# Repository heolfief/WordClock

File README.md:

# 8x8 Dot Matrix Word Clock
This is an AVR based mini word clock featuring:
* Real Time Clock (DS3231)
* LiPo battery with integrated USB charging circuit
* low battery sensing

The unit is composed of two stacked PCB and one 8x8 dot-matrix display module.

The Hardware folder is composed of Autodesk Eagle CAD files (schematics and PCB) and of Bill Of Materials.

The Software folder is composed of Atmel Studio 7.0 project files, including libraries and hex file.

The I2C-master-lib is from user g4lvanix on Github ([github.com/g4lvanix/I2C-master-lib](http://github.com/g4lvanix/I2C-master-lib)). However, he does not include any licence in his repository therefore all rights for this library belongs to him.
All other libraries included are under the licence descibed in the LICENCE.md file.

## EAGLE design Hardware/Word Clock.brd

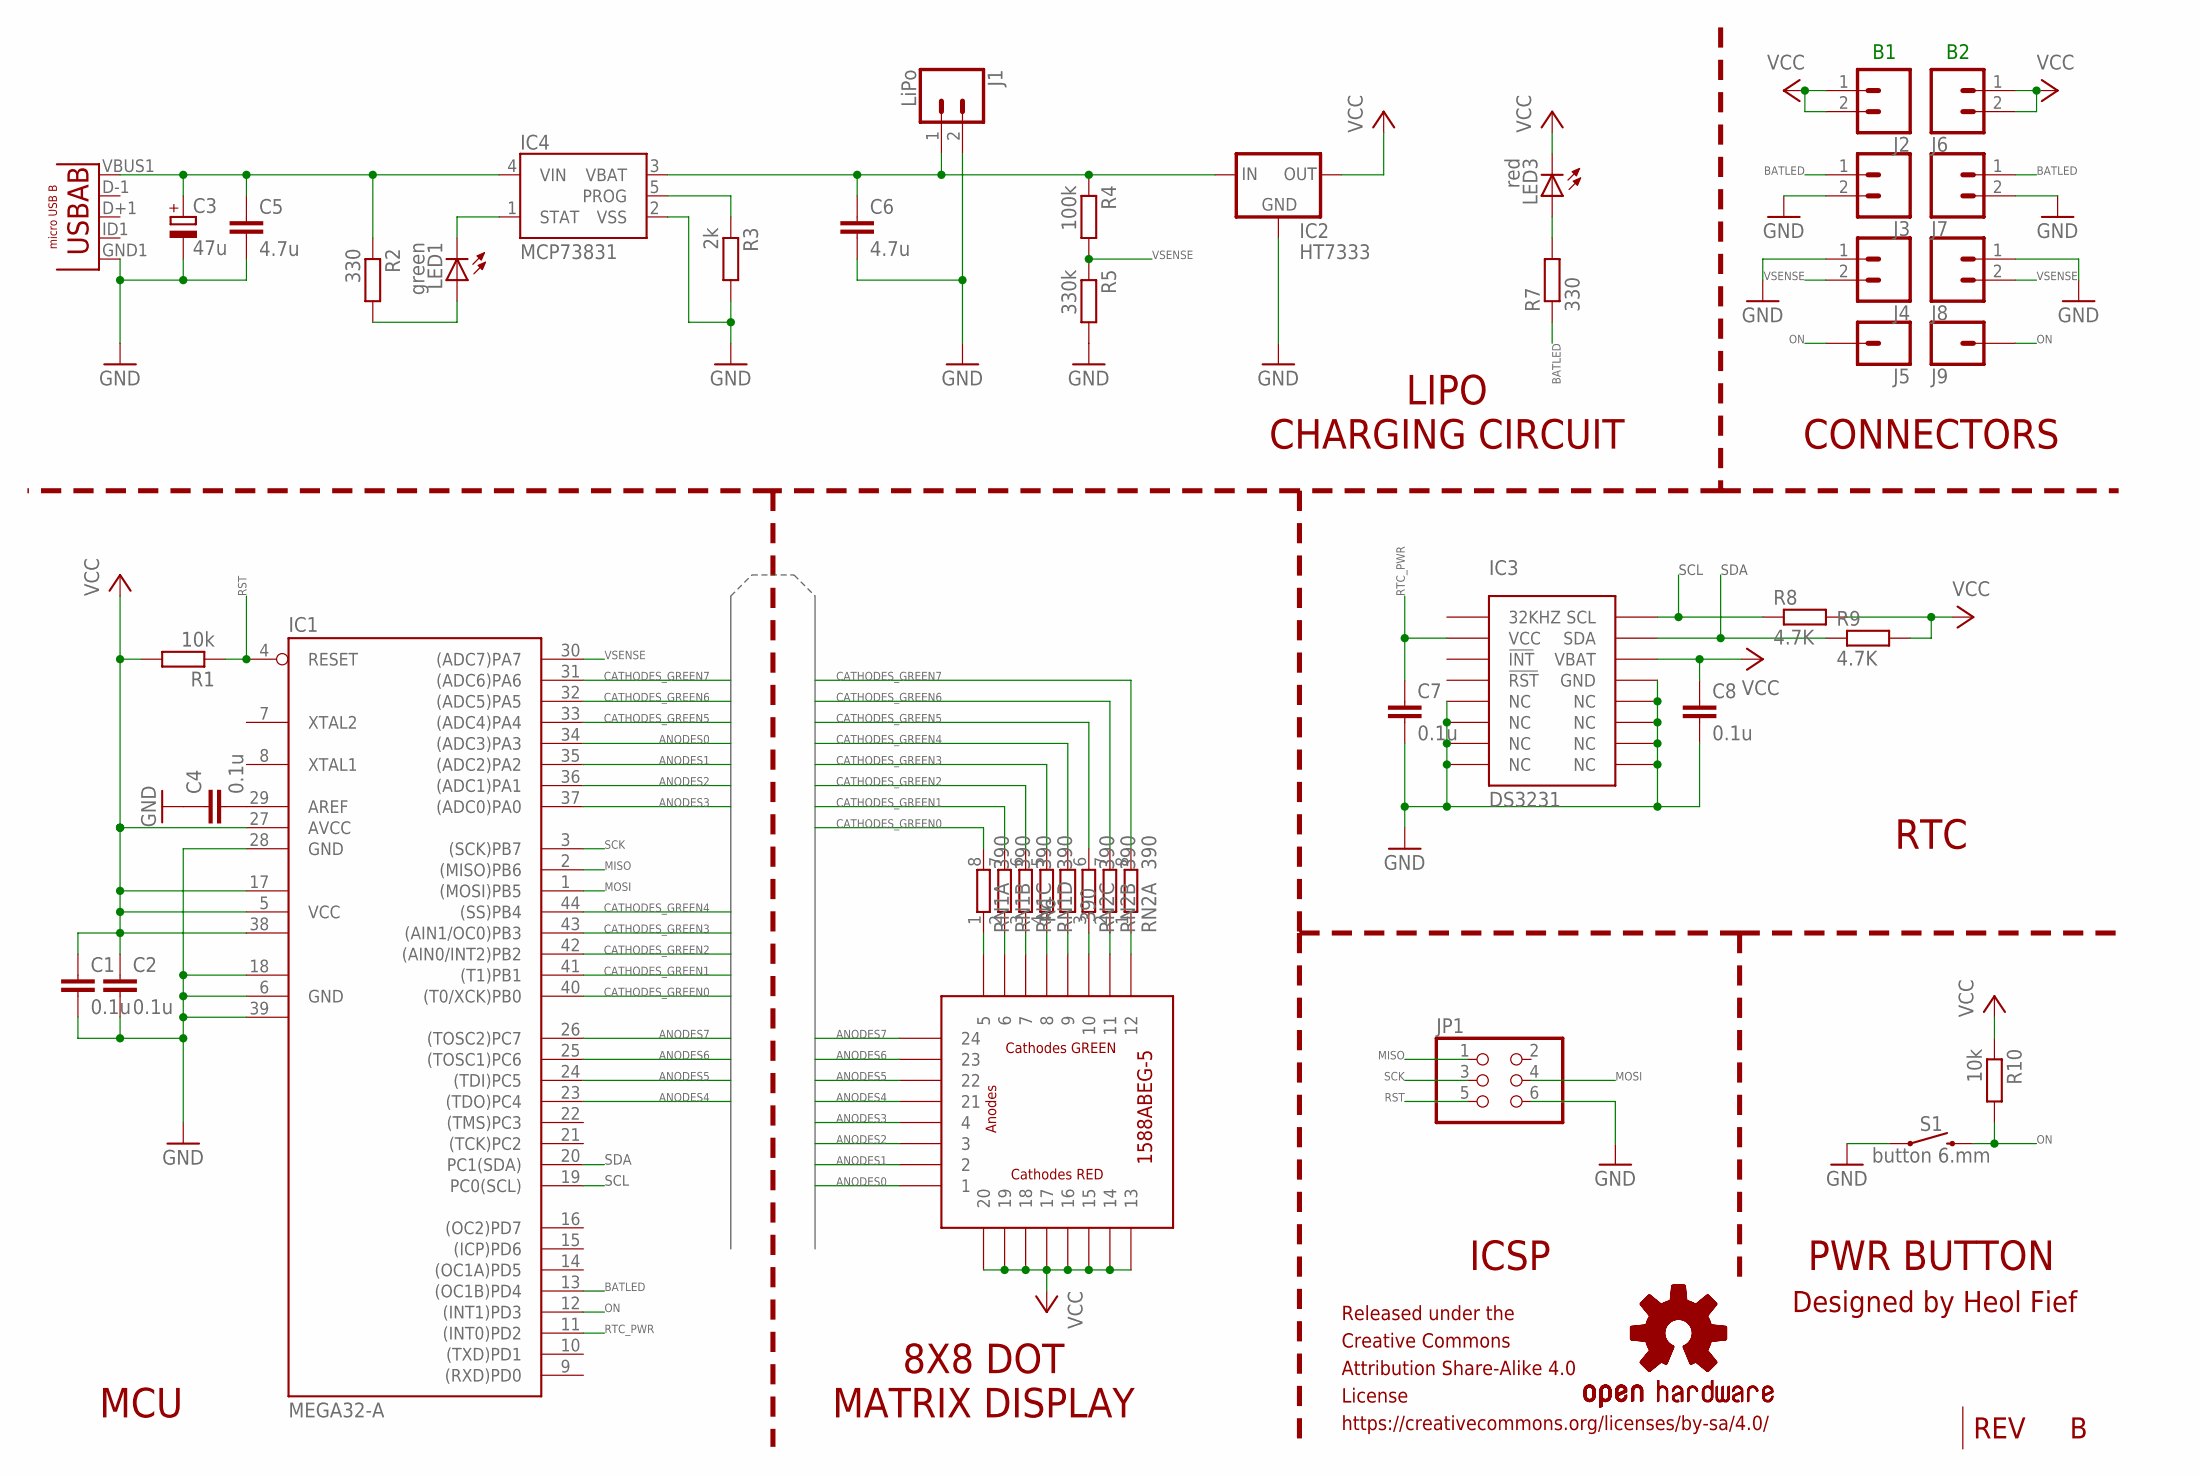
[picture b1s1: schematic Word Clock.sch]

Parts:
C1, C2, C4, C7, C8: 0.1u; C0805
C3: 47u; D/7343-31W
C5, C6: 4.7u; C0805
IC1: MEGA32-A; TQFP44
IC2: HT7333; SOT-89
IC3: DS3231; SOIC-16W
IC4: MCP73831; SOT23-5
J1: LiPo; MOLEX-1X2
J2, J3, J4, J6, J7, J8: CONN_02; 1X02
J5, J9: CONN_01; 1X01
J10: USB""; USB-MICRO-SMD
JP1: PINHD-2X3/90; 2X03/90
LED1: green; CHIPLED_1206
LED2: 1588ABEG-5_8X8-LED_MATRIX
LED3: red; CHIPLED_1206
LOGO1, LOGO2: OSHW-LOGOL-COPPER; OSHW-LOGO-L_COPPER
R1, R10: 10k; M0805
R2, R7: 330; M0805
R3: 2k; M0805
R4: 100k; M0805
R5: 330k; M0805
R6: 390; R0805
R8, R9: 4.7K; M0805
RN1, RN2: 390; 0603-ARC
S1: button 6.mm; TACTILE_SWITCH_PTH_6.0MM

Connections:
ANODES0: IC1.34 ((ADC3)PA3), LED2.P$1 (1)
ANODES1: IC1.35 ((ADC2)PA2), LED2.P$2 (2)
ANODES2: IC1.36 ((ADC1)PA1), LED2.P$3 (3)
ANODES3: IC1.37 ((ADC0)PA0), LED2.P$4 (4)
ANODES4: IC1.23 ((TDO)PC4), LED2.P$21 (21)
ANODES5: IC1.24 ((TDI)PC5), LED2.P$22 (22)
ANODES6: IC1.25 ((TOSC1)PC6), LED2.P$23 (23)
ANODES7: IC1.26 ((TOSC2)PC7), LED2.P$24 (24)
AREF: C4.2, IC1.29 (AREF)
BATLED: IC1.13 ((OC1B)PD4), J3.1, J7.1, R7.1
CATHODES_GREEN0: IC1.40 ((T0/XCK)PB0), RN1.8 (2)
CATHODES_GREEN1: IC1.41 ((T1)PB1), RN1.7 (2)
CATHODES_GREEN2: IC1.42 ((AIN0/INT2)PB2), RN1.6 (2)
CATHODES_GREEN3: IC1.43 ((AIN1/OC0)PB3), RN1.5 (2)
CATHODES_GREEN4: IC1.44 ((SS)PB4), R6.2
CATHODES_GREEN5: IC1.33 ((ADC4)PA4), RN2.6 (2)
CATHODES_GREEN6: IC1.32 ((ADC5)PA5), RN2.7 (2)
CATHODES_GREEN7: IC1.31 ((ADC6)PA6), RN2.8 (2)
GND: C1.2, C2.2, C3.-, C4.1, C5.2, C6.2, C7.2, C8.2, IC1.6 (GND), IC1.18 (GND1), IC1.28 (GND), IC1.39 (GND2), IC2.2 (GND), IC3.5 (NC), IC3.6 (NC), IC3.7 (NC), IC3.8 (NC), IC3.9 (NC), IC3.10 (NC), IC3.11 (NC), IC3.12 (NC), IC3.13 (GND), IC4.2 (VSS), J1.2, J3.2, J4.1, J7.2, J8.1, J10.GND1 (GND), JP1.6, R3.2, R5.2, S1.1, S1.2 (1)
MISO: IC1.2 ((MISO)PB6), JP1.1
MOSI: IC1.1 ((MOSI)PB5), JP1.4
unnamed: LED2.P$5 (5), RN1.1
unnamed: IC4.5 (PROG), R3.1
unnamed: LED2.P$6 (6), RN1.2 (1)
unnamed: LED2.P$7 (7), RN1.3 (1)
unnamed: C6.1, IC2.3 (IN), IC2.4 (IN), IC4.3 (VBAT), J1.1, R4.1
unnamed: LED2.P$8 (8), RN1.4 (1)
unnamed: LED1.A, R2.2
unnamed: IC4.1 (STAT), LED1.C
unnamed: C3.+, C5.1, IC4.4 (VIN), J10.VBUS1 (VBUS), R2.1
unnamed: LED2.P$9 (9), R6.1
unnamed: LED2.P$10 (10), RN2.3 (1)
unnamed: LED2.P$11 (11), RN2.2 (1)
unnamed: LED2.P$12 (12), RN2.1
unnamed: LED3.A, R7.2
ON: IC1.12 ((INT1)PD3), J5.1, J9.1, R10.2, S1.3 (2), S1.4 (2)
RST: IC1.4 (RESET), JP1.5, R1.1
RTC_PWR: C7.1, IC1.11 ((INT0)PD2), IC3.2 (VCC)
SCK: IC1.3 ((SCK)PB7), JP1.3
SCL: IC1.19 (PC0(SCL)), IC3.16 (SCL), R8.1
SDA: IC1.20 (PC1(SDA)), IC3.15 (SDA), R9.1
VCC: C1.1, C2.1, C8.1, IC1.5 (VCC), IC1.17 (VCC1), IC1.27 (AVCC), IC1.38 (VCC2), IC2.1 (OUT), IC3.14 (VBAT), J2.1, J2.2, J6.1, J6.2, LED2.P$13 (13), LED2.P$14 (14), LED2.P$15 (15), LED2.P$16 (16), LED2.P$17 (17), LED2.P$18 (18), LED2.P$19 (19), LED2.P$20 (20), LED3.C, R1.2, R8.2, R9.2, R10.1
VSENSE: IC1.30 ((ADC7)PA7), J4.2, J8.2, R4.2, R5.1

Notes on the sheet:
MCU
8X8 DOT MATRIX DISPLAY
PWR BUTTON
RTC
ICSP
LIPO CHARGING CIRCUIT
CONNECTORS
REV
Designed by Heol Fief
Released under the Creative Commons Attribution Share-Alike 4.0 License https://creativecommons.org/licenses/by-sa/4.0/
micro USB B

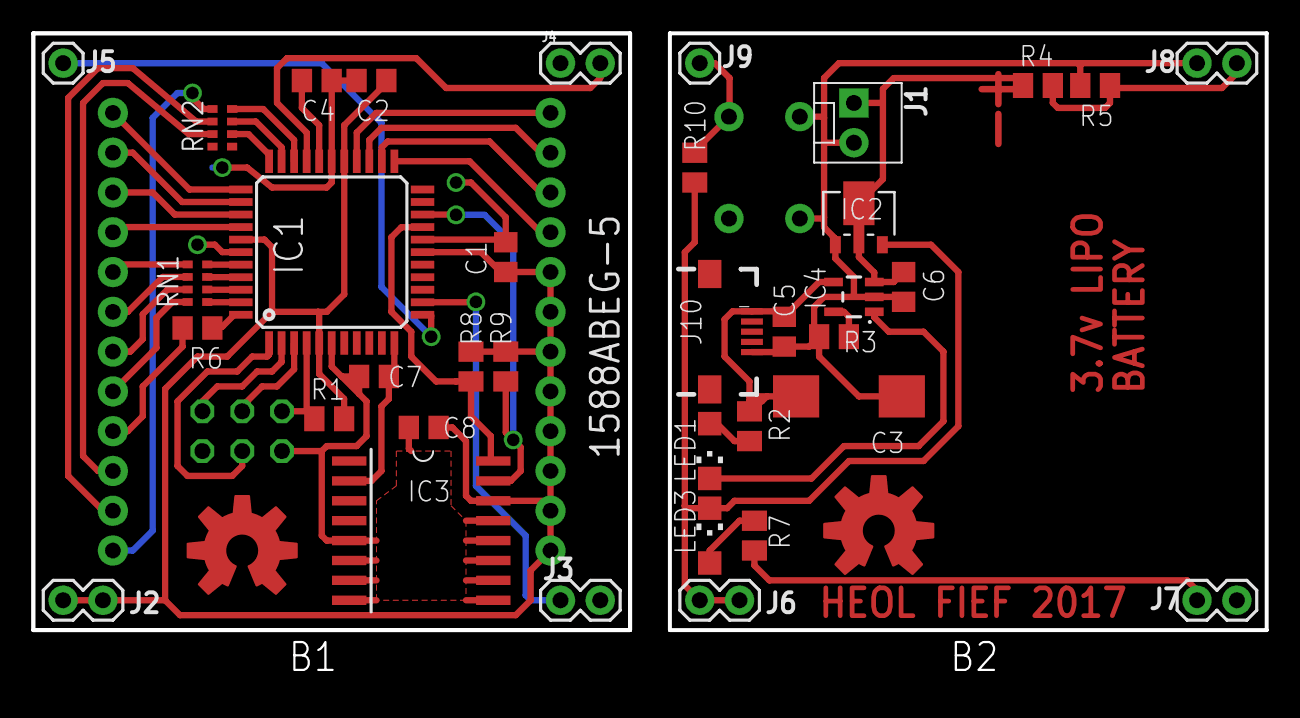
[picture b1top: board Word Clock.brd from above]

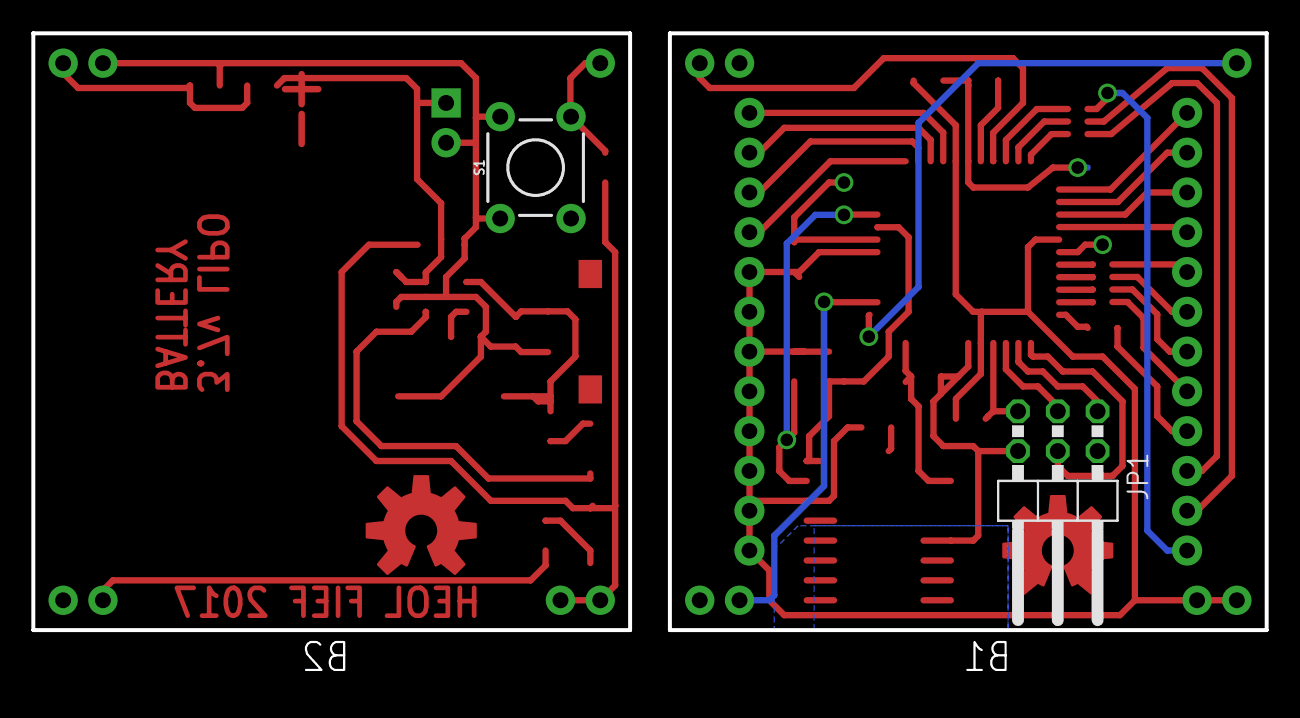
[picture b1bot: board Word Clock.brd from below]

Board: 2 copper layers, 78.7 x 41.6 mm, 41 parts (2 on the bottom side), 43 nets.

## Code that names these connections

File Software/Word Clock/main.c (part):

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*		OUTPUT PINS CONFIGURATION AND 8X8 MATRIX LETTERS CONFGURATION
*
*
*	PORTS	PB0		PB1		PB2		PB3		PB4		PA4		PA5		PA6
*	PORTS	___		___		___		___		___		___		___		___
*
*	PC7	|	 H		 A		 T		 W		 E		 N		 T		 Y
*
*
*	PC6	|	 F		 I		 F		 V		 T		 E		 E		 N
*
*
*	PC5	|	 L		 F		 X		 P		 A		 S		 T		 O
*
*
*	PC4	|	 N		 I		 N		 E		 I		 G		 H		 T
*
*
*	PA0	|	 O		 N		 E		 T		 H		 R		 E		 E
*
*
*	PA1	|	 T		 W		 E		 L		 E		 V		 E		 N
*
*
*	PA2	|	 F		 O		 U		 R		 F		 I		 V		 E
*
*
*	PA3	|	 S		 I		 X		 S		 E		 V		 E		 N
*
*/

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
	io_setup();									// Configure the MCU's GPIO
	
	PORTD |= (1<<PD2);							// Give power to RTC
	i2c_init();									// Initialize I2C communication
	PORTD &= ~(1<<PD2);							// Cut power to RTC	
		
	while (1)
	{
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		
		check_battery(&low_battery, &critical_battery);
		
		if(low_battery) PORTD &= ~(1<<PD4);		// if battery level is low, turn ON a LED and run the program
		
		if(critical_battery)					// if battery level is critical, blink a LED ON and OFF and don't run the program
		{
			for(i=0; i<10; i++)					// Number of LED blinks
			{
				PORTD ^= (1<<PD4);				// Invert output state of PD4 (connected to LED cathode)
				_delay_ms(250);					// Wait 250ms
			}
			PORTD |= (1<<PD4);					// Turn OFF LED (output 5v to LED cathode)
		}
		else									// If battery level is good
		{
			PORTD |= (1<<PD2);					// Give power to RTC
			i2c_init();							// Initialize I2C communication
			rtc_get_time_12h(&hour, &min, &sec, &am_pm);	// Get time
			PORTD &= ~(1<<PD2);					// Cut power to RTC
			
			minutes_to_matrix(min, data);		// Convert minutes to the data array to be displayed on the LED matrix
			if(min>35)hour++;					// If minutes are more than half an hour, then add an hour to the display
			hours_to_matrix(hour, data);		// Convert hours to the data array to be displayed on the LED matrix
			display(data, 1000);					// Display the data array for 10s (1251)
			
			if (bit_is_clear(PIND,PD3))			// If button is still pressed
			{
				MCUCR |= (1<<ISC11);			// ...
				MCUCR &= ~(1<<ISC10);			// ... Enable interrupt on falling edge of INT1
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				cli();                         	// Disable interrupts
				setmode=0;						// Exit setmode
				
				PORTD |= (1<<PD2);				// Give power to RTC
				rtc_set_time_12h(hour,min,0,0);	// Set new time to RTC
				PORTD &= ~(1<<PD2);				// Cut power to RTC
			}
		}
	}
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
void sleep()
{
	PORTD |= (1<<PD4);							// Turn OFF LED on PD4 (output 5v to LED cathode)
	
	ACSR |= (1<<ACD);          					// Disable Analog comparator	
	
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
void io_setup()
{
	DDRA = 0x7F;								// PORTA as output except PA7 as input
	DDRB = 0xFF;								// PORTB as output
	DDRC = 0xFC;								// PORTC as output
	DDRD = 0x14;								// PD3 as input, PD4 and PD2 as outputs
	
	PORTA = 0x00;								// All outputs low
	PORTB = 0x00;								// All outputs low
	PORTC = 0x00;								// All outputs low
	PORTD = 0x10;								// All outputs low except PD4 (led OFF)
	PORTD |= (1<<PD3);							// Enable pullup on PD3
}

void check_battery(uint8_t *lowbat, uint8_t *critbat)
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
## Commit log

2017-04-30 Create newfolder
2017-04-30 Add files via upload
    Add schematics and board files (Eagle format)
2017-04-30 Update Eagle files
2017-04-30 Update README.md
    Add library licence explanations
2017-04-30 Add code comments
2017-04-30 Format comments
2017-05-01 Add comments
2017-05-01 Add files via upload
    PCB print files, ready to print and transfer on PCB.
    TOP is mirrored, BOTTOM is not
2017-05-01 Clean silkscreen
2017-08-17 Rename editorconfig to .editorconfig
2017-10-29 Add a time-set function
    Long press (10s) on the button make the device enter time-set mode. You no longer require to reflash firmware to set the time.

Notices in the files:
parts and their libraries:
SparkFun-Connectors: Licensing: Creative Commons ShareAlike 4.0 International - https://creativecommons.org/licenses/by-sa/4.0
